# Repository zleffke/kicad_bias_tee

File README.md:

# kicad_bias_tee
Bias Tee KiCAD designs for biasing RF devices via coaxial cable.

## References
- [Reeve Observatory - Long Wavelength Array Active Crossed-Dipole Antenna](http://www.reeve.com/RadioScience/Antennas/ActiveCrossed-Dipole/LWA_Antenna.htm)
- [Long Wavelength Array (LWA) Memo Series](https://www.faculty.ece.vt.edu/swe/lwa/)
- [Bias-T Design Considerations for the LWA by Brian Hicks, Bill Erickson](https://www.faculty.ece.vt.edu/swe/lwa/memo/lwa0135.pdf)

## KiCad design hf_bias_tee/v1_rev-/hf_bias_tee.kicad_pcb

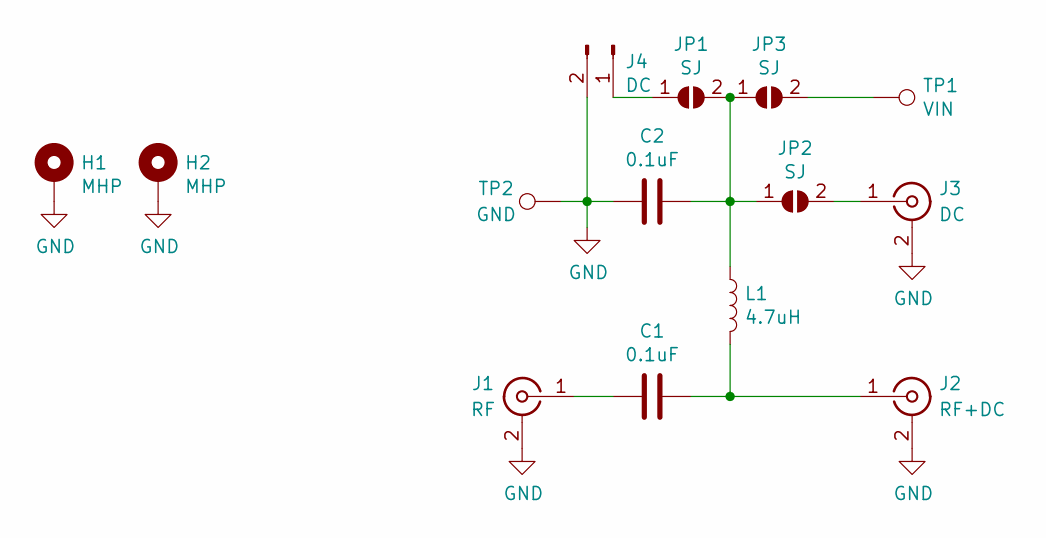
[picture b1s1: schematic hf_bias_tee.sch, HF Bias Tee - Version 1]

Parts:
C1, C2: 0.1uF; 0805
H1, H2: MHP; MountingHole_2.2mm_M2_Pad_Via
J1: RF; SMA_Amphenol_132134_Vertical
J2: RF+DC; SMA_Amphenol_132134_Vertical
J3: DC; SMA_Amphenol_132134_Vertical
J4: DC; PinSocket_1x02_P2.54mm_Vertical
JP1, JP2, JP3: SJ; SolderJumper-2_P1.3mm_Open_RoundedPad1.0x1.5mm
L1: 4.7uH; L_1008_2520Metric
TP1: VIN; TestPoint_Pad_2.0x2.0mm
TP2: GND; TestPoint_Pad_2.0x2.0mm

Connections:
GND: C2.2, H1.1, H2.1, J1.2 (Ext), J2.2 (Ext), J3.2 (Ext), J4.2, TP2.1
unnamed: C1.1, J2.1 (In), L1.2
unnamed: C1.2, J1.1 (In)
unnamed: C2.1, JP1.2 (B), JP2.1 (A), JP3.1 (A), L1.1
unnamed: J3.1 (In), JP2.2 (B)
unnamed: J4.1, JP1.1 (A)
unnamed: JP3.2 (B), TP1.1

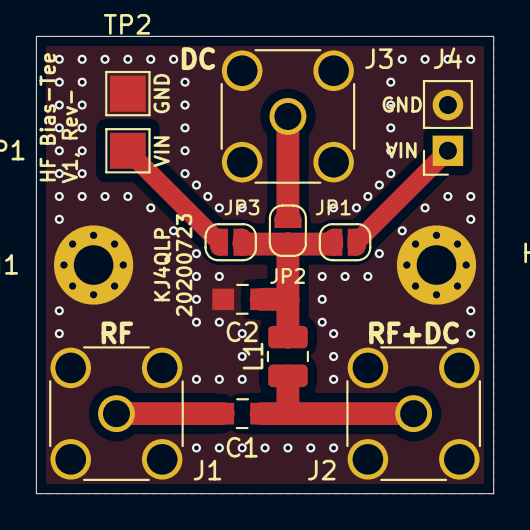
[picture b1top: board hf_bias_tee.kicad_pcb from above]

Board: 2 copper layers, 25.4 x 25.4 mm, 14 parts (0 on the bottom side), 7 nets.

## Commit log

2020-07-23 Commit of V1, Rev-. Sent to Osh Park for fab.

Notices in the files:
hf_bias_tee/v1_rev-/hf_bias_tee.kicad_pcb:
License: CC BY 4.0
hf_bias_tee/v1_rev-/hf_bias_tee.sch:
creativecommons.org/licenses/by/4.0
